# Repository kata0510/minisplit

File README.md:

minisplit
---
6×4 +1keys Split Keyboard
 
PCBSize:132mm×75mm

Parts
---
・PCB 2  
・KeySwitch 50  
・Diode 50 (1N4148,1N4148W)  
・ProMicro 2  
・TRRS Jack 2 (MJ-4PP-9,PJ320A)  
・TACT Switch 1 (P-08073)

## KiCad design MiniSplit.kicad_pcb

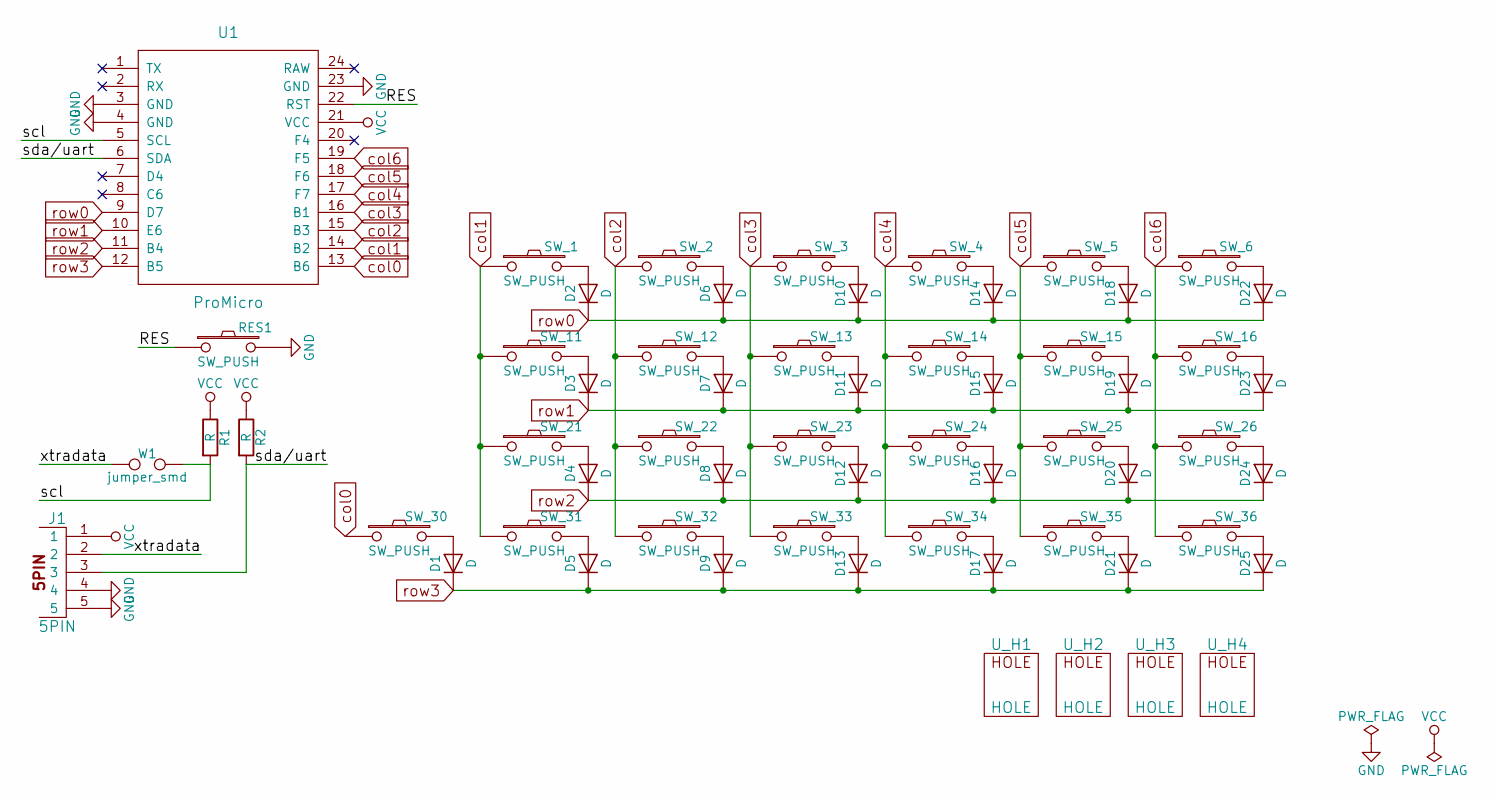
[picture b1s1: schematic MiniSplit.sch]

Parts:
D1, D2, D3, D4, D5, D6, D7, D8, D9, D10, D11, D12, D13, D14, D15, D16, D17, D18, D19, D20, D21, D22, D23, D24, D25: D; Diode_TH_SOD123
J1: 5PIN; TRRS_JACK_MJ4PP9
R1, R2: R; RESISTOR
RES1: SW_PUSH; TACT_SWITCH_TVBP06
SW_1, SW_2, SW_3, SW_4, SW_5, SW_6, SW_11, SW_12, SW_13, SW_14, SW_15, SW_16, SW_21, SW_22, SW_23, SW_24, SW_25, SW_26, SW_30, SW_31, SW_32, SW_33, SW_34, SW_35, SW_36: SW_PUSH; MX_PG1350_FLIP_HOLES
U1: ProMicro
U_H1, U_H2, U_H3, U_H4: HOLE; hole
W1: jumper_smd; jumper_smd_2dub

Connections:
/RES: RES1.1, U1.22 (RST); also elsewhere on the board
/scl: R1.2, U1.5 (SCL), W1.2; also elsewhere on the board
/sda/uart: J1.3, R2.2, U1.6 (SDA); also elsewhere on the board
/xtradata: J1.2, W1.1
GND: J1.4, J1.5, RES1.2, U1.3 (GND), U1.4 (GND), U1.23 (GND); also elsewhere on the board
unnamed: D1.2 (A), SW_30.2
unnamed: D2.2 (A), SW_1.2
unnamed: D3.2 (A), SW_11.2
unnamed: D4.2 (A), SW_21.2
unnamed: D5.2 (A), SW_31.2
unnamed: D6.2 (A), SW_2.2
unnamed: D7.2 (A), SW_12.2
unnamed: D8.2 (A), SW_22.2
unnamed: D9.2 (A), SW_32.2
unnamed: D10.2 (A), SW_3.2
unnamed: D11.2 (A), SW_13.2
unnamed: D12.2 (A), SW_23.2
unnamed: D13.2 (A), SW_33.2
unnamed: D14.2 (A), SW_4.2
unnamed: D15.2 (A), SW_14.2
unnamed: D16.2 (A), SW_24.2
unnamed: D17.2 (A), SW_34.2
unnamed: D18.2 (A), SW_5.2
unnamed: D19.2 (A), SW_15.2
unnamed: D20.2 (A), SW_25.2
unnamed: D21.2 (A), SW_35.2
unnamed: D22.2 (A), SW_6.2
unnamed: D23.2 (A), SW_16.2
unnamed: D24.2 (A), SW_26.2
unnamed: D25.2 (A), SW_36.2
VCC: J1.1, R1.1, R2.1, U1.21 (VCC); also elsewhere on the board
col0: SW_30.1, U1.13 (B6); also elsewhere on the board
col1: SW_1.1, SW_11.1, SW_21.1, SW_31.1, U1.14 (B2); also elsewhere on the board
col2: SW_2.1, SW_12.1, SW_22.1, SW_32.1, U1.15 (B3); also elsewhere on the board
col3: SW_3.1, SW_13.1, SW_23.1, SW_33.1, U1.16 (B1); also elsewhere on the board
col4: SW_4.1, SW_14.1, SW_24.1, SW_34.1, U1.17 (F7); also elsewhere on the board
col5: SW_5.1, SW_15.1, SW_25.1, SW_35.1, U1.18 (F6); also elsewhere on the board
col6: SW_6.1, SW_16.1, SW_26.1, SW_36.1, U1.19 (F5); also elsewhere on the board
row0: D2.1 (K), D6.1 (K), D10.1 (K), D14.1 (K), D18.1 (K), D22.1 (K), U1.9 (D7); also elsewhere on the board
row1: D3.1 (K), D7.1 (K), D11.1 (K), D15.1 (K), D19.1 (K), D23.1 (K), U1.10 (E6); also elsewhere on the board
row2: D4.1 (K), D8.1 (K), D12.1 (K), D16.1 (K), D20.1 (K), D24.1 (K), U1.11 (B4); also elsewhere on the board
row3: D1.1 (K), D5.1 (K), D9.1 (K), D13.1 (K), D17.1 (K), D21.1 (K), D25.1 (K), U1.12 (B5); also elsewhere on the board

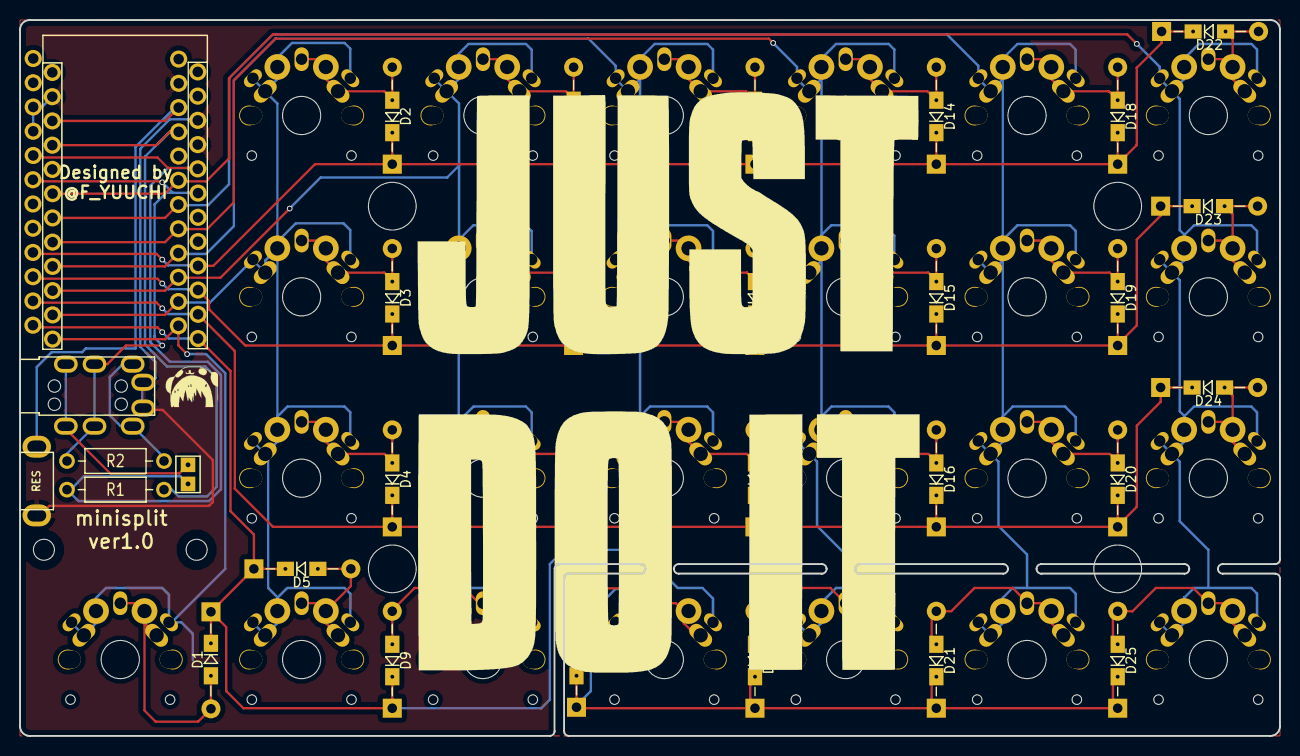
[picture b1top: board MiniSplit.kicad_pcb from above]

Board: 2 copper layers, 132.0 x 75.0 mm, 61 parts (1 on the bottom side), 42 nets.

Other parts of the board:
U1#2: ProMicro

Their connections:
/RES: U1#2.22; also elsewhere on the board
/scl: U1#2.5; also elsewhere on the board
/sda/uart: U1#2.6; also elsewhere on the board
GND: U1#2.3, U1#2.4, U1#2.23; also elsewhere on the board
VCC: U1#2.21; also elsewhere on the board
col0: U1#2.13; also elsewhere on the board
col1: U1#2.14; also elsewhere on the board
col2: U1#2.15; also elsewhere on the board
col3: U1#2.16; also elsewhere on the board
col4: U1#2.17; also elsewhere on the board
col5: U1#2.18; also elsewhere on the board
col6: U1#2.19; also elsewhere on the board
row0: U1#2.9; also elsewhere on the board
row1: U1#2.10; also elsewhere on the board
row2: U1#2.11; also elsewhere on the board
row3: U1#2.12; also elsewhere on the board

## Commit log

2018-01-22 add image
2018-01-23 add casefile
2018-01-24 ✨ver0.1→0.2✨
    fix:Switch Hole,TRRS Jack Silk
    add:icon
2018-01-24 fix file
2018-01-24 add file
2018-01-24 fix #1 #2
2018-01-24 fix #2
2018-01-24 fix #1
2018-01-24 📝Change Image
    Image:ver0.1PCB→0.2PCB
2018-01-29 SizeCange
    130mm×85mm→127mm×83.5mm
2018-01-31 cutdata update
    3set cutting data
2018-03-04 deletefile
2018-03-04 renewal casefile
2018-03-04 renewal gerberfile
2018-03-04 update and add Libraryfile
2018-03-04 update LICENSE
2018-03-04 ✨ver0.2→1.0✨
    42keys→50keys
2018-07-21 size fixed
